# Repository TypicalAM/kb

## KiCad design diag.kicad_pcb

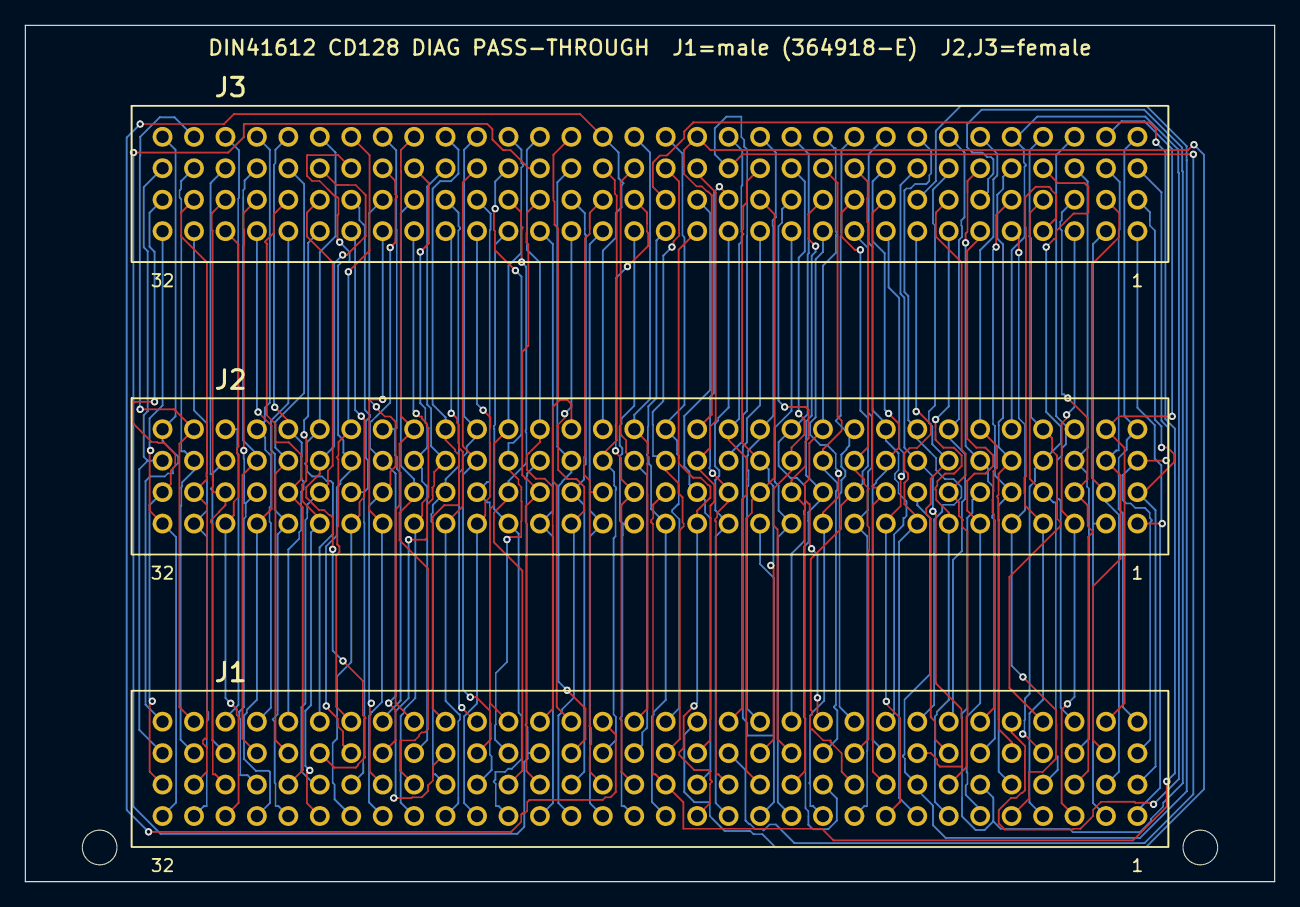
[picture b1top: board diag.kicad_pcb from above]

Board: 2 copper layers, 100.9 x 69.2 mm, 3 parts (0 on the bottom side), 128 nets.

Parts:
J1: MALE_RA_364918-E
J2, J3: FEMALE_128

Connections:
a1: J1.a1, J2.a1, J3.a1
a2: J1.a2, J2.a2, J3.a2
a3: J1.a3, J2.a3, J3.a3
a4: J1.a4, J2.a4, J3.a4
a5: J1.a5, J2.a5, J3.a5
a6: J1.a6, J2.a6, J3.a6
a7: J1.a7, J2.a7, J3.a7
a8: J1.a8, J2.a8, J3.a8
a9: J1.a9, J2.a9, J3.a9
a10: J1.a10, J2.a10, J3.a10
a11: J1.a11, J2.a11, J3.a11
a12: J1.a12, J2.a12, J3.a12
a13: J1.a13, J2.a13, J3.a13
a14: J1.a14, J2.a14, J3.a14
a15: J1.a15, J2.a15, J3.a15
a16: J1.a16, J2.a16, J3.a16
a17: J1.a17, J2.a17, J3.a17
a18: J1.a18, J2.a18, J3.a18
a19: J1.a19, J2.a19, J3.a19
a20: J1.a20, J2.a20, J3.a20
a21: J1.a21, J2.a21, J3.a21
a22: J1.a22, J2.a22, J3.a22
a23: J1.a23, J2.a23, J3.a23
a24: J1.a24, J2.a24, J3.a24
a25: J1.a25, J2.a25, J3.a25
a26: J1.a26, J2.a26, J3.a26
a27: J1.a27, J2.a27, J3.a27
a28: J1.a28, J2.a28, J3.a28
a29: J1.a29, J2.a29, J3.a29
a30: J1.a30, J2.a30, J3.a30
a31: J1.a31, J2.a31, J3.a31
a32: J1.a32, J2.a32, J3.a32
b1: J1.b1, J2.b1, J3.b1
b2: J1.b2, J2.b2, J3.b2
b3: J1.b3, J2.b3, J3.b3
b4: J1.b4, J2.b4, J3.b4
b5: J1.b5, J2.b5, J3.b5
b6: J1.b6, J2.b6, J3.b6
b7: J1.b7, J2.b7, J3.b7
b8: J1.b8, J2.b8, J3.b8
b9: J1.b9, J2.b9, J3.b9
b10: J1.b10, J2.b10, J3.b10
b11: J1.b11, J2.b11, J3.b11
b12: J1.b12, J2.b12, J3.b12
b13: J1.b13, J2.b13, J3.b13
b14: J1.b14, J2.b14, J3.b14
b15: J1.b15, J2.b15, J3.b15
b16: J1.b16, J2.b16, J3.b16
b17: J1.b17, J2.b17, J3.b17
b18: J1.b18, J2.b18, J3.b18
b19: J1.b19, J2.b19, J3.b19
b20: J1.b20, J2.b20, J3.b20
b21: J1.b21, J2.b21, J3.b21
b22: J1.b22, J2.b22, J3.b22
b23: J1.b23, J2.b23, J3.b23
b24: J1.b24, J2.b24, J3.b24
b25: J1.b25, J2.b25, J3.b25
b26: J1.b26, J2.b26, J3.b26
b27: J1.b27, J2.b27, J3.b27
b28: J1.b28, J2.b28, J3.b28
b29: J1.b29, J2.b29, J3.b29
b30: J1.b30, J2.b30, J3.b30
b31: J1.b31, J2.b31, J3.b31
b32: J1.b32, J2.b32, J3.b32
c1: J1.c1, J2.c1, J3.c1
c2: J1.c2, J2.c2, J3.c2
c3: J1.c3, J2.c3, J3.c3
c4: J1.c4, J2.c4, J3.c4
c5: J1.c5, J2.c5, J3.c5
c6: J1.c6, J2.c6, J3.c6
c7: J1.c7, J2.c7, J3.c7
c8: J1.c8, J2.c8, J3.c8
c9: J1.c9, J2.c9, J3.c9
c10: J1.c10, J2.c10, J3.c10
c11: J1.c11, J2.c11, J3.c11
c12: J1.c12, J2.c12, J3.c12
c13: J1.c13, J2.c13, J3.c13
c14: J1.c14, J2.c14, J3.c14
c15: J1.c15, J2.c15, J3.c15
c16: J1.c16, J2.c16, J3.c16
c17: J1.c17, J2.c17, J3.c17
c18: J1.c18, J2.c18, J3.c18
c19: J1.c19, J2.c19, J3.c19
c20: J1.c20, J2.c20, J3.c20
c21: J1.c21, J2.c21, J3.c21
c22: J1.c22, J2.c22, J3.c22
c23: J1.c23, J2.c23, J3.c23
c24: J1.c24, J2.c24, J3.c24
c25: J1.c25, J2.c25, J3.c25
c26: J1.c26, J2.c26, J3.c26
c27: J1.c27, J2.c27, J3.c27
c28: J1.c28, J2.c28, J3.c28
c29: J1.c29, J2.c29, J3.c29
c30: J1.c30, J2.c30, J3.c30
c31: J1.c31, J2.c31, J3.c31
c32: J1.c32, J2.c32, J3.c32
d1: J1.d1, J2.d1, J3.d1
d2: J1.d2, J2.d2, J3.d2
d3: J1.d3, J2.d3, J3.d3
d4: J1.d4, J2.d4, J3.d4
d5: J1.d5, J2.d5, J3.d5
d6: J1.d6, J2.d6, J3.d6
d7: J1.d7, J2.d7, J3.d7
d8: J1.d8, J2.d8, J3.d8
d9: J1.d9, J2.d9, J3.d9
d10: J1.d10, J2.d10, J3.d10
d11: J1.d11, J2.d11, J3.d11
d12: J1.d12, J2.d12, J3.d12
d13: J1.d13, J2.d13, J3.d13
d14: J1.d14, J2.d14, J3.d14
d15: J1.d15, J2.d15, J3.d15
d16: J1.d16, J2.d16, J3.d16
d17: J1.d17, J2.d17, J3.d17
d18: J1.d18, J2.d18, J3.d18
d19: J1.d19, J2.d19, J3.d19
d20: J1.d20, J2.d20, J3.d20
d21: J1.d21, J2.d21, J3.d21
d22: J1.d22, J2.d22, J3.d22
d23: J1.d23, J2.d23, J3.d23
d24: J1.d24, J2.d24, J3.d24
d25: J1.d25, J2.d25, J3.d25
d26: J1.d26, J2.d26, J3.d26
d27: J1.d27, J2.d27, J3.d27
d28: J1.d28, J2.d28, J3.d28
d29: J1.d29, J2.d29, J3.d29
d30: J1.d30, J2.d30, J3.d30
d31: J1.d31, J2.d31, J3.d31
d32: J1.d32, J2.d32, J3.d32
